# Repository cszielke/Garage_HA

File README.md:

# Garage_HA
Garage home automation

## Sensors:
* Auto Präsenz/Abstand
* Tor zu
* Temperatur

## Aktor:
* Tor
* Außenlicht
* Kompressor

## Sonstiges
* Webcam

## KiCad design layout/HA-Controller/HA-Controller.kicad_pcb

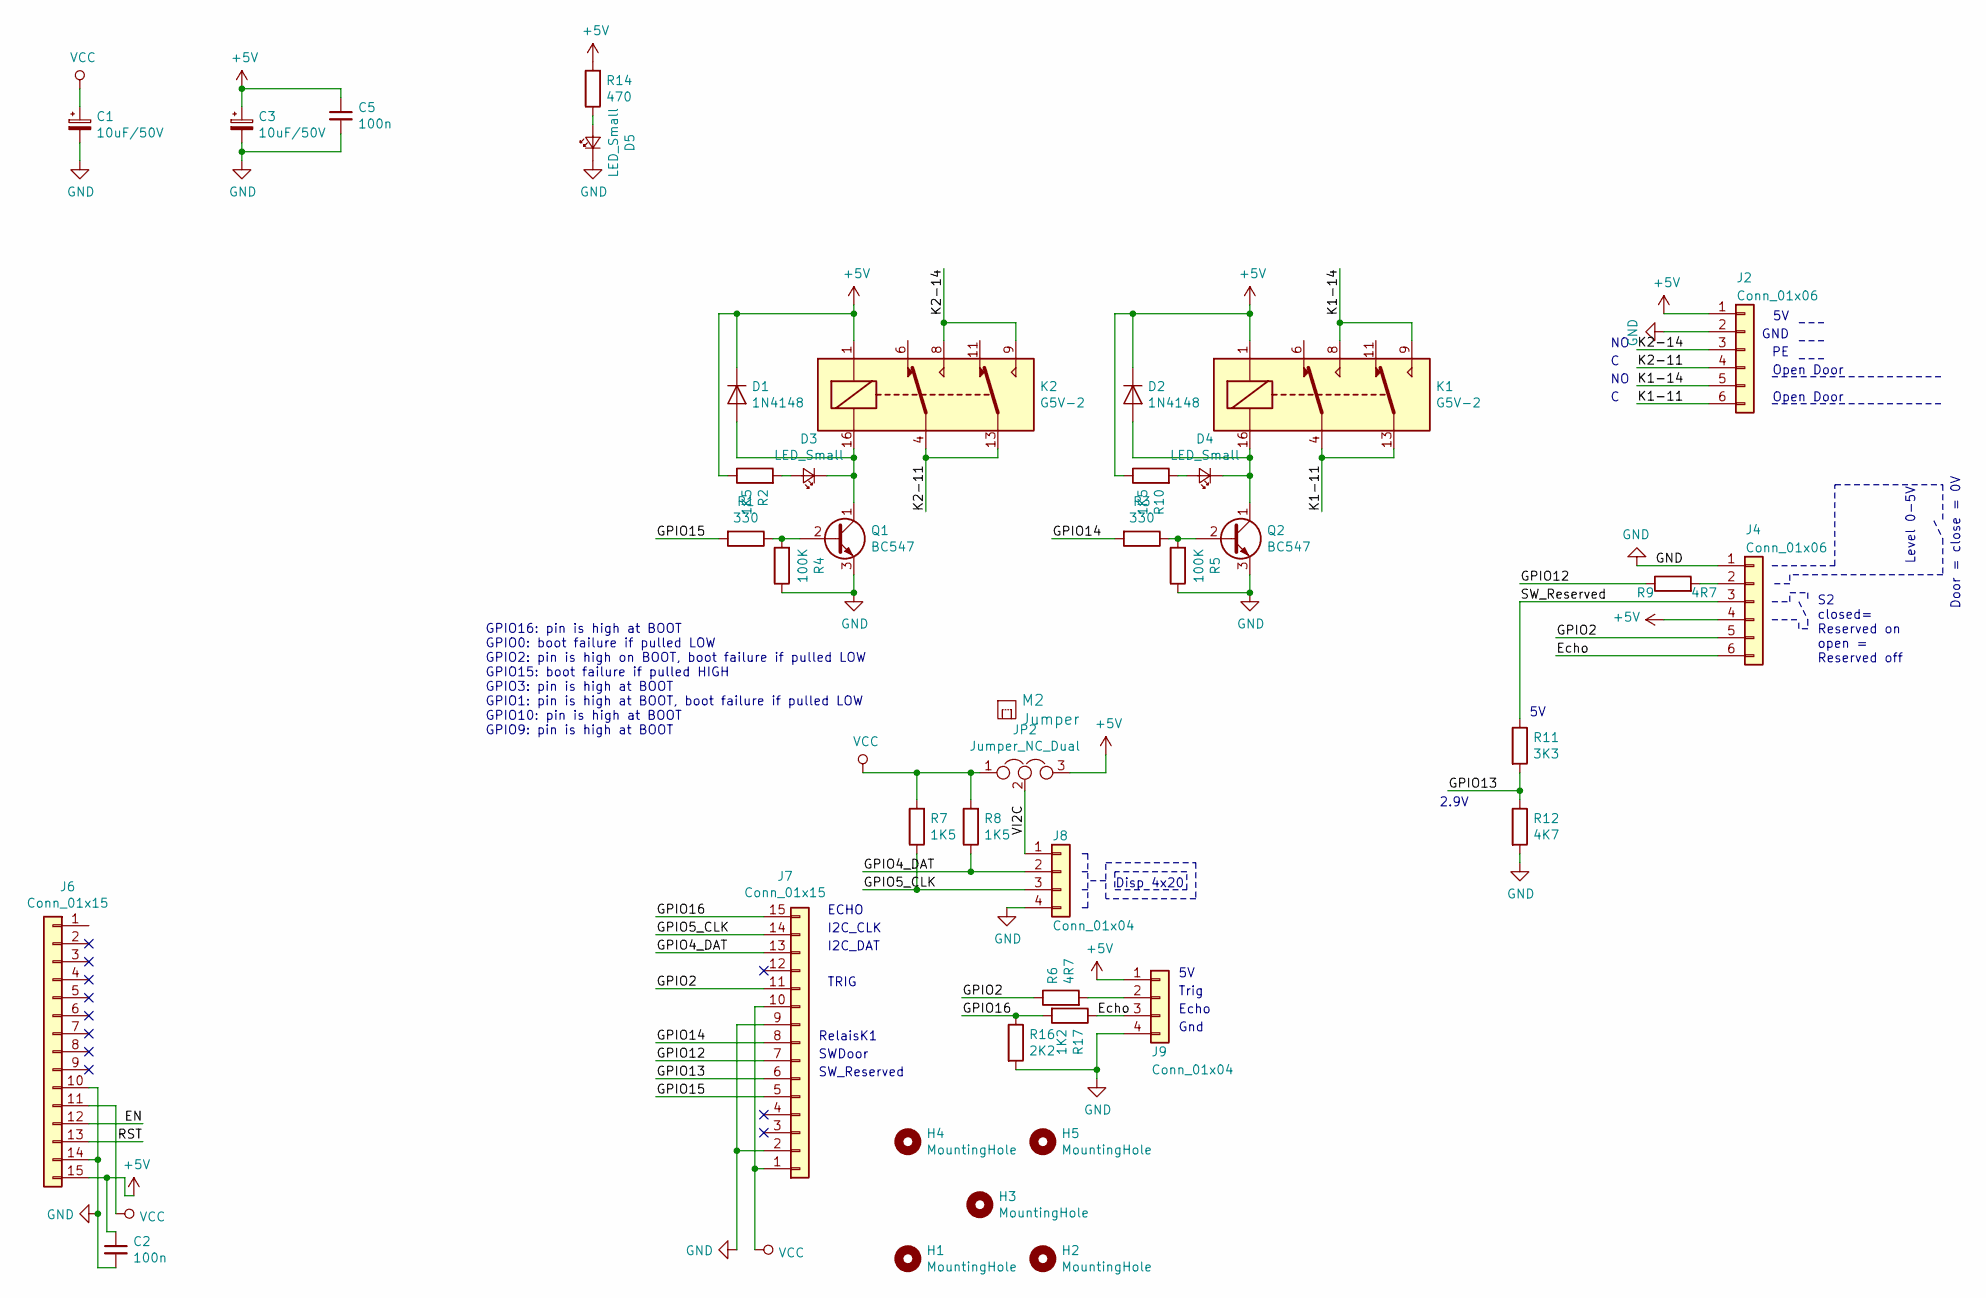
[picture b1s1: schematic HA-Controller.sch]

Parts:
C1, C3: 10uF/50V; CP_Radial_D6.3mm_P2.50mm
C2, C5: 100n; C_0603_1608Metric
D1, D2: 1N4148; D_DO-35_SOD27_P7.62mm_Horizontal
D3, D4, D5: LED_Small; LED_D3.0mm
H1, H2, H3, H4, H5: MountingHole; MountingHole_4.3mm_M4_ISO14580
J2, J4: Conn_01x06; PhoenixContact_MSTBA_2,5_6-G-5,08_1x06_P5.08mm_Horizontal
J6, J7: Conn_01x15; PinSocket_1x15_P2.54mm_Vertical
J8, J9: Conn_01x04; WR-WTB-04-V
JP2: Jumper_NC_Dual; PinHeader_1x03_P2.54mm_Vertical
K1, K2: G5V-2; Relay_DPDT_Omron_G5V-2
M2: Jumper
Q1, Q2: BC547; TO-92_Inline
R1, R3: 330; R_0603_1608Metric
R2, R7, R8, R10: 1K5; R_0603_1608Metric
R4, R5: 100K; R_0603_1608Metric
R6, R9: 4R7; R_0603_1608Metric
R11: 3K3; R_0603_1608Metric
R12: 4K7; R_0603_1608Metric
R14: 470; R_0603_1608Metric
R16: 2K2; R_0603_1608Metric
R17: 1K2; R_0603_1608Metric

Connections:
+5V: C2.1, C3.1, C5.1, D1.1 (K), D2.1 (K), J2.1, J4.4, J6.15, J9.1, JP2.3, K1.1, K2.1, R2.1, R10.1, R14.2
/EN: J6.12
/Echo: J4.6, J9.3, R17.1
/GPIO2: J4.5, J7.11, R6.1
/GPIO4_DAT: J7.13, J8.2, R8.1
/GPIO5_CLK: J7.14, J8.3, R7.1
/GPIO12: J7.7, R9.1
/GPIO13: J7.6, R11.2, R12.1
/GPIO14: J7.8, R3.2
/GPIO15: J7.5, R1.2
/GPIO16: J7.15, R16.1, R17.2
/K1-11: J2.6, K1.4, K1.13
/K1-14: J2.5, K1.8, K1.9
/K2-11: J2.4, K2.4, K2.13
/K2-14: J2.3, K2.8, K2.9
/RST: J6.13
/SW_Reserved: J4.3, R11.1
/VI2C: J8.1, JP2.2
GND: C1.2, C2.2, C3.2, C5.2, D5.1 (K), J2.2, J4.1, J6.10, J6.14, J7.2, J7.9, J8.4, J9.4, Q1.3 (E), Q2.3 (E), R4.1, R5.1, R12.2, R16.2
unnamed: D1.2 (A), D3.1 (K), K2.16, Q1.1 (C)
unnamed: D2.2 (A), D4.1 (K), K1.16, Q2.1 (C)
unnamed: D3.2 (A), R2.2
unnamed: D4.2 (A), R10.2
unnamed: D5.2 (A), R14.1
unnamed: J4.2, R9.2
unnamed: J9.2, R6.2
unnamed: Q1.2 (B), R1.1, R4.2
unnamed: Q2.2 (B), R3.1, R5.2
VCC: C1.1, J6.11, J7.1, J7.10, JP2.1, R7.2, R8.2

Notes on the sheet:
I2C_DAT
I2C_CLK
SWDoor
2.9V
Open Door
S2 closed= Reserved on open = Reserved off
Level 0-5V
Door = close = 0V
Disp 4x20
RelaisK1
SW_Reserved
TRIG
GPIO16: pin is high at BOOT GPIO0: boot failure if pulled LOW GPIO2: pin is high on BOOT, boot failure if pulled LOW GPIO15: boot failure if pulled HIGH GPIO3: pin is high at BOOT GPIO1: pin is high at BOOT, boot failure if pulled LOW GPIO10: pin is high at BOOT GPIO9: pin is high at BOOT
ECHO
Trig
Echo
Gnd
GND

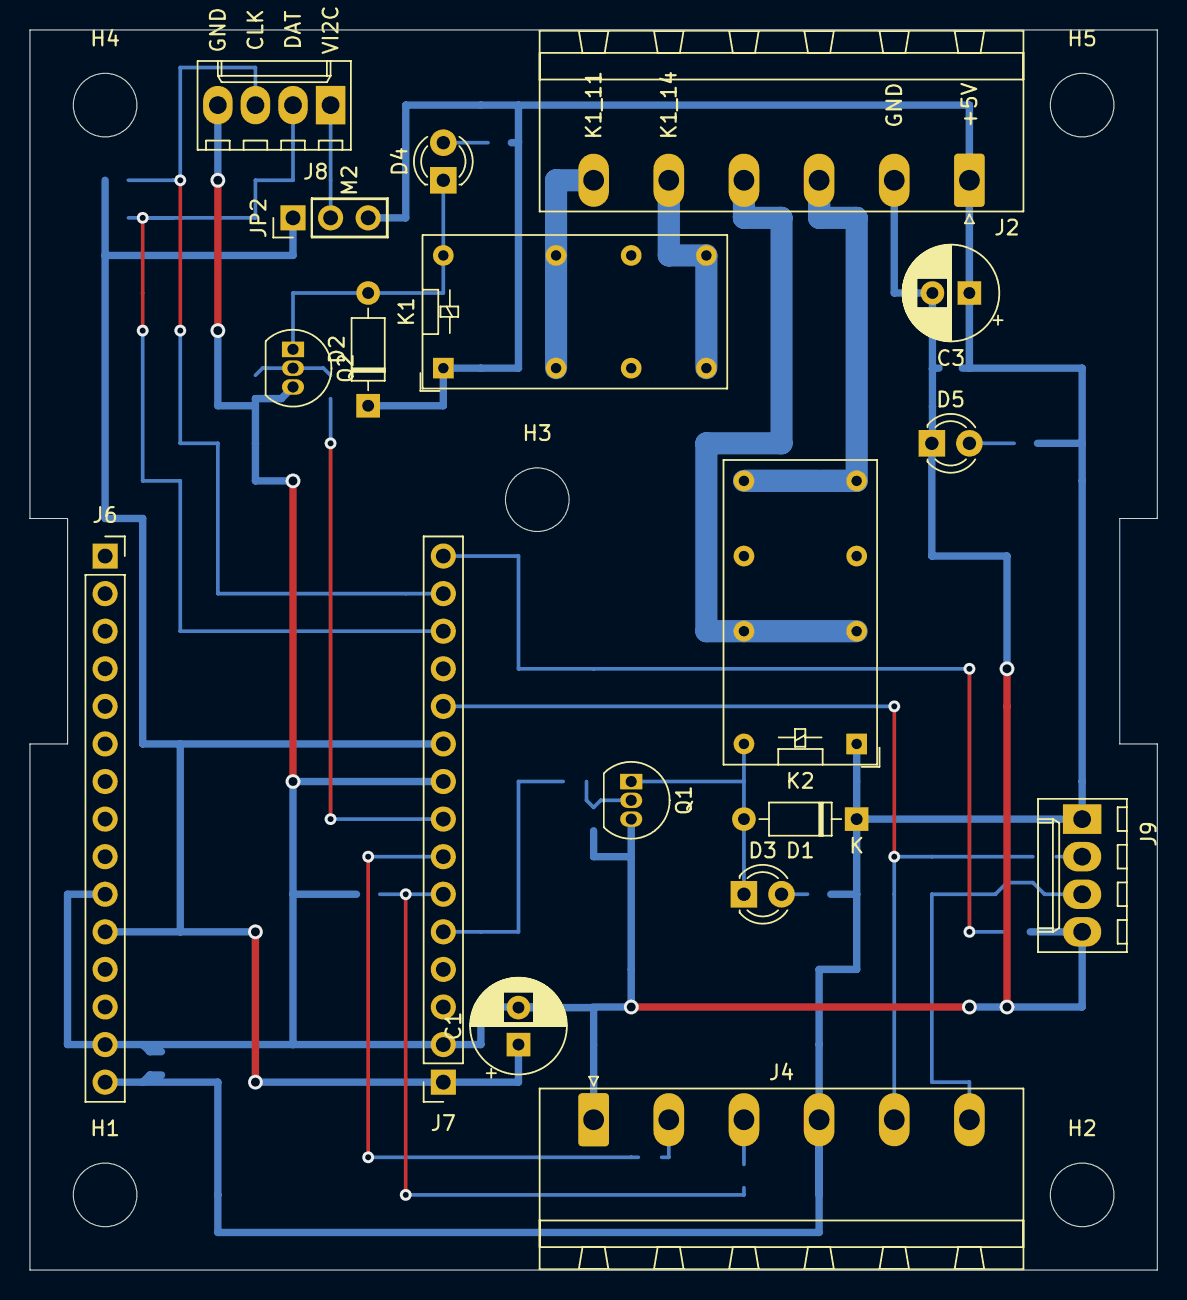
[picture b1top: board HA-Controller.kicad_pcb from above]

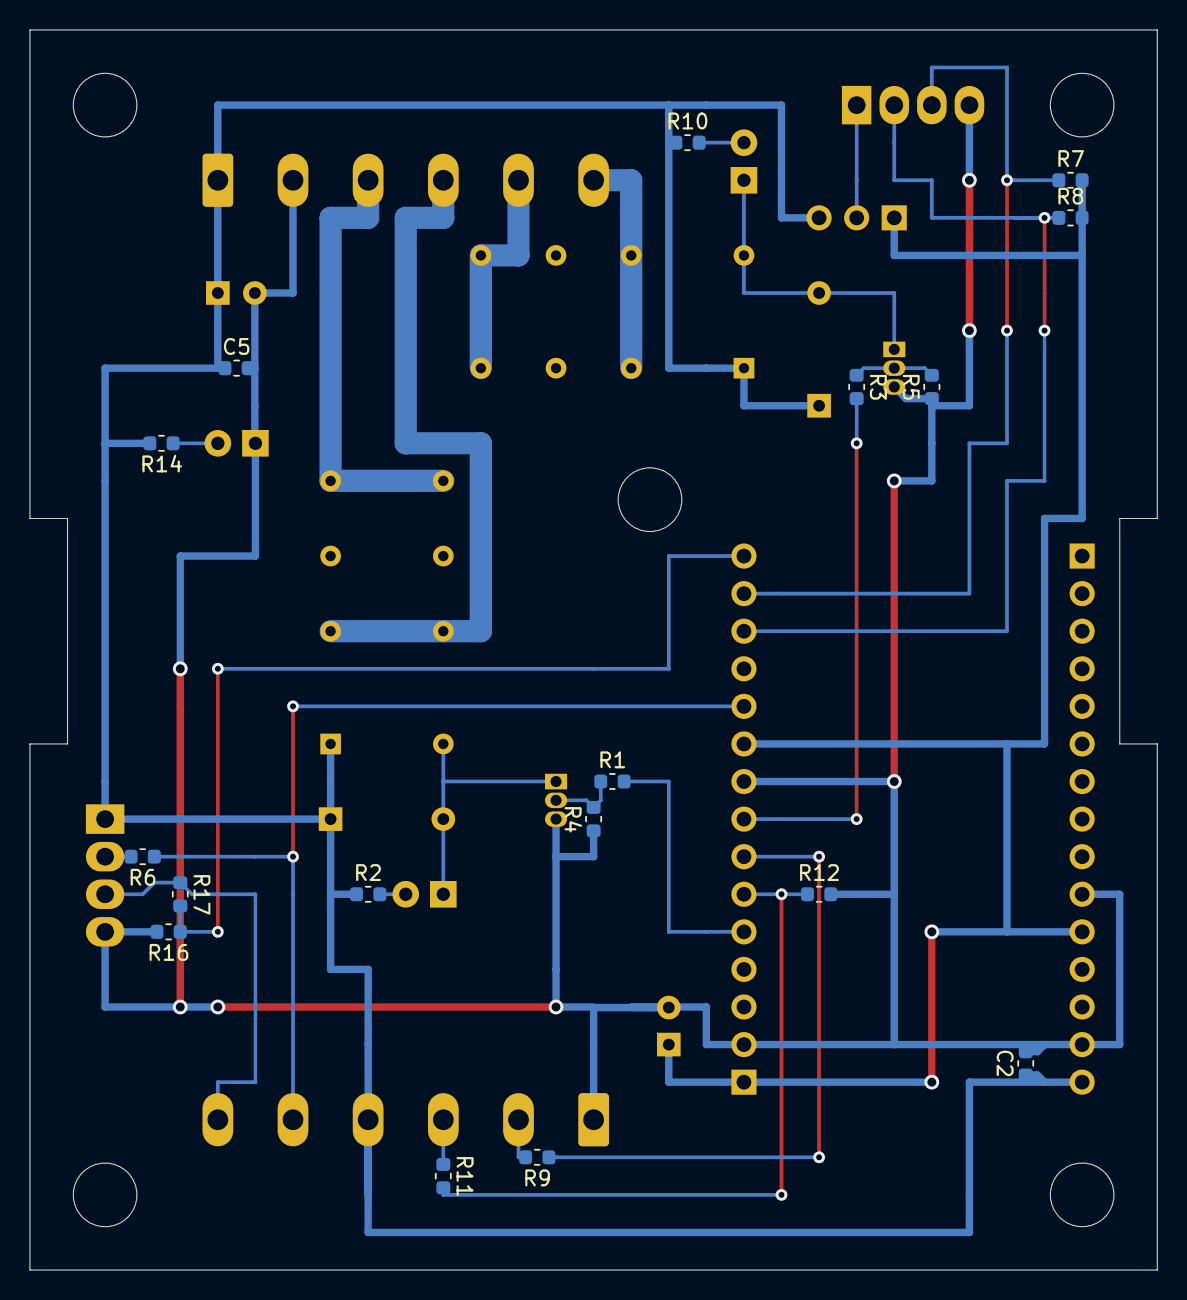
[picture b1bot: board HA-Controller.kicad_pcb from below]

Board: 2 copper layers, 76.2 x 83.8 mm, 41 parts (17 on the bottom side), 27 nets.

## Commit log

2021-04-22 Initial Checkin
2021-04-22 First functional version
2021-04-27 Falsche GPIO Nr korrigiert, MQTT Screenshot
2021-04-27 Layout abgespeckt
2021-05-02 Übertragung der Feldstärke per MQTT
2021-05-08 Layout für Verteilerdose und Lochraster optimiert
2021-05-12 Option mit Wemos D1-Mini
2021-05-13 Erste Inbetriebnahme
